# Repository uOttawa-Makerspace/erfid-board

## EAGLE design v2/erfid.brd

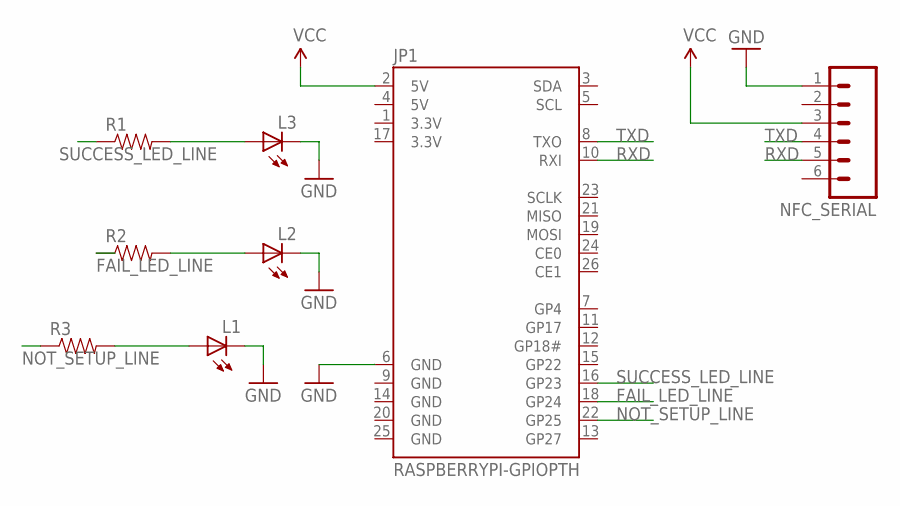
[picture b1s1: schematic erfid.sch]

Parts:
JP1: RASPBERRYPI-GPIOPTH; 2X13-SHROUDED
L1, L2, L3: LED5MM
NFC_SERIAL: M06SILK_FEMALE_PTH; 1X06
R1, R2, R3: RESISTORPTH-1/4W; AXIAL-0.4

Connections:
3.3V: JP1.1 (3.3V), JP1.17 (3.3V)
5V: JP1.4 (5V)
FAIL_LED_LINE: JP1.18 (GP24), R2.P$1 (1)
GND: JP1.6 (GND), JP1.9 (GND), JP1.14 (GND), JP1.20 (GND), JP1.25 (GND), L1.K (C), L2.K (C), L3.K (C), NFC_SERIAL.1
unnamed: L2.A, R2.P$2 (2)
unnamed: L3.A, R1.P$2 (2)
unnamed: L1.A, R3.P$2 (2)
NOT_SETUP_LINE: JP1.22 (GP25), R3.P$1 (1)
RXD: JP1.10 (RXI), NFC_SERIAL.5
SUCCESS_LED_LINE: JP1.16 (GP23), R1.P$1 (1)
TXD: JP1.8 (TXO), NFC_SERIAL.4
VCC: JP1.2 (5V), NFC_SERIAL.3

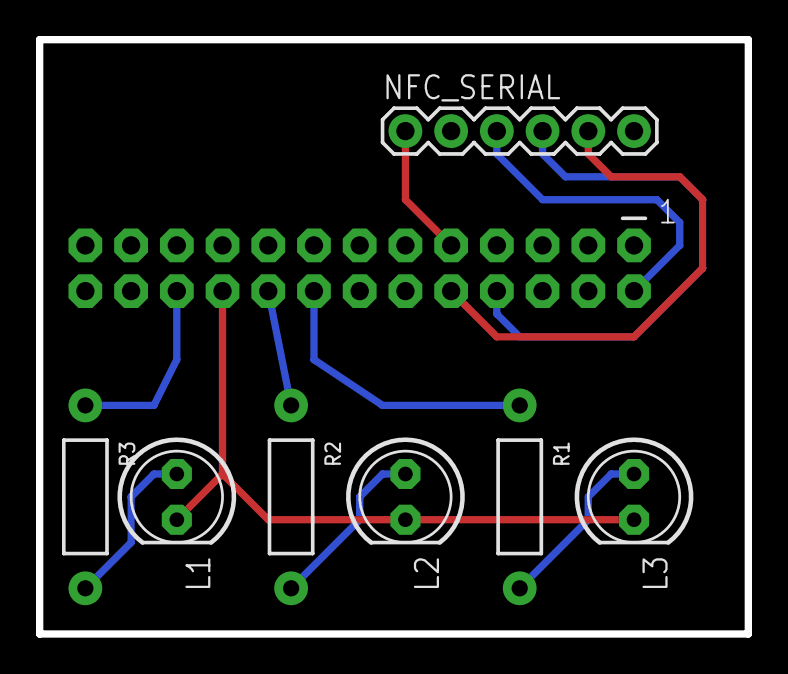
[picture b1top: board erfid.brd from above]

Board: 2 copper layers, 39.4 x 33.0 mm, 8 parts (0 on the bottom side), 11 nets.

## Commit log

2017-08-21 all the designs
2021-04-29 Added SVG Case

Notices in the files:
parts and their libraries:
SparkFun-Boards: Licensing: Creative Commons ShareAlike 4.0 International - https://creativecommons.org/licenses/by-sa/4.0
